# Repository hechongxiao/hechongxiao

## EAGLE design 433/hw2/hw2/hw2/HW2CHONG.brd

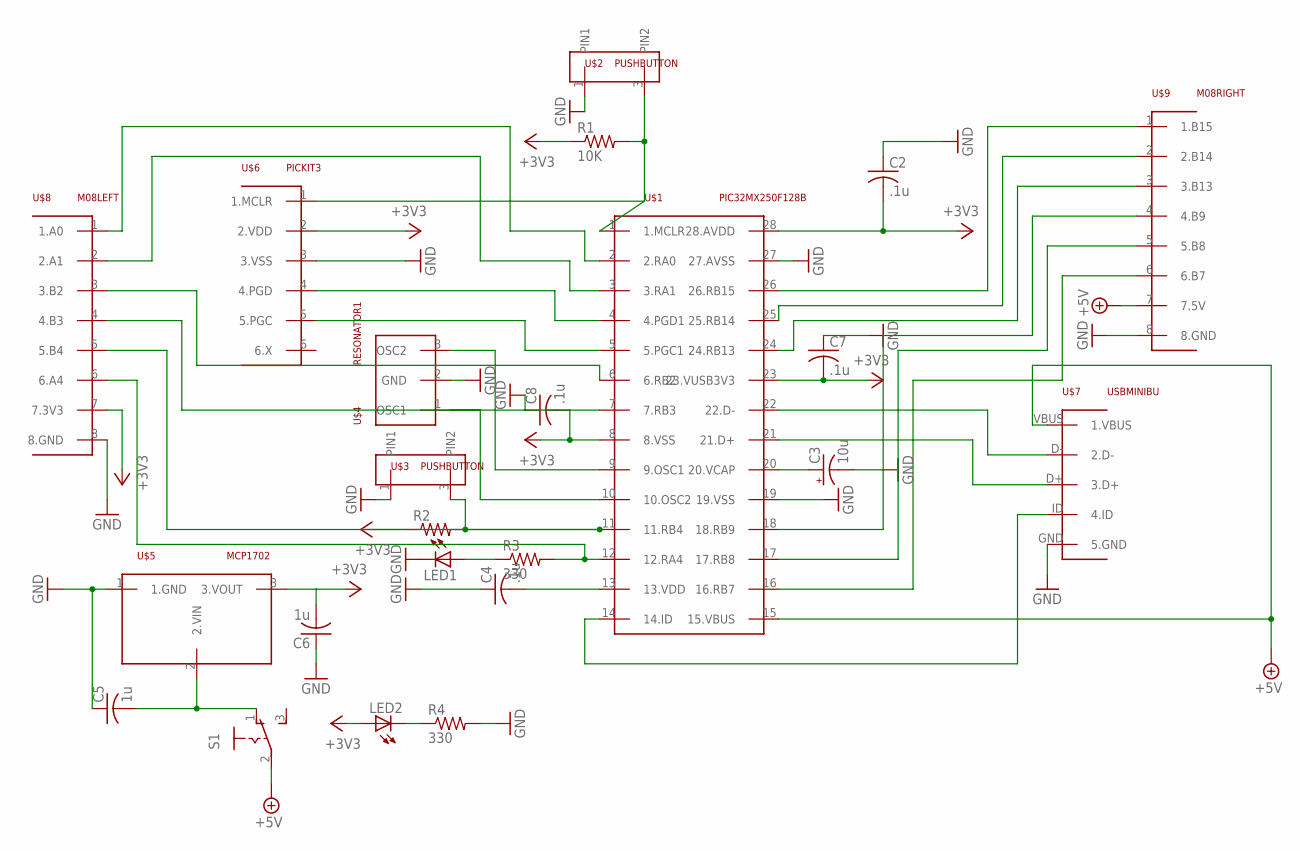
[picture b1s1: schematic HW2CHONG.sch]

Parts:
C2, C4, C7, C8: .1u; C025-025X050
C3: 10u; B45181A
C5, C6: 1u; C025-025X050
LED1, LED2: LED3MM
R1: 10K; 0207/10
R2: R-US_0207/10; 0207/10
R3, R4: 330; 0207/10
S1: 255SB
U$1: PIC32MX250F128B; DIL28-3
U$2, U$3: PUSHBUTTON; 1X03
U$4: RESONATOR1; 1X03
U$5: MCP1702; TO92
U$6: PICKIT3; 1X06
U$7: USBMINIBU; USB-MB-H
U$8: M08LEFT; 1X08
U$9: M08RIGHT; 1X08

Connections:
+3V3: C2.2, C7.2, C8.2, LED2.A, R1.1, R2.1, U$1.8 (8.VSS), U$1.23 (23.VUSB3V3), U$1.28 (28.AVDD), U$6.2 (2.VDD), U$8.7 (7.3V3)
+5V: S1.2, U$1.15 (15.VBUS), U$7.VBUS (1.VBUS), U$9.7 (7.5V)
GND: C2.1, C3.-, C4.1, C5.1, C6.1, C7.1, C8.1, LED1.K (C), R4.2, U$1.19 (19.VSS), U$1.27 (27.AVSS), U$2.1 (PIN1), U$3.1 (PIN1), U$4.2 (GND), U$5.1 (1.GND), U$6.3 (3.VSS), U$7.GND (5.GND), U$8.8 (8.GND), U$9.8 (8.GND)
unnamed: LED1.A, R3.1
unnamed: R3.2, U$1.12 (12.RA4), U$8.6 (6.A4)
unnamed: R1.2, U$1.1 (1.MCLR), U$2.3 (PIN2), U$6.1 (1.MCLR)
unnamed: C3.+, U$1.20 (20.VCAP)
unnamed: R2.2, U$1.11 (11.RB4), U$3.3 (PIN2), U$8.5 (5.B4)
unnamed: C4.2, U$1.13 (13.VDD)
unnamed: C6.2, U$5.3 (3.VOUT)
unnamed: U$1.10 (10.OSC2), U$4.1 (OSC1)
unnamed: U$1.9 (9.OSC1), U$4.3 (OSC2)
unnamed: U$1.4 (4.PGD1), U$6.4 (4.PGD)
unnamed: U$1.5 (5.PGC1), U$6.5 (5.PGC)
unnamed: U$1.22 (22.D-), U$7.D- (2.D-)
unnamed: U$1.21 (21.D+), U$7.D+ (3.D+)
unnamed: U$1.14 (14.ID), U$7.ID (4.ID)
unnamed: U$1.2 (2.RA0), U$8.1 (1.A0)
unnamed: C5.2, S1.1 (O), U$5.2 (2.VIN)
unnamed: LED2.K (C), R4.1
unnamed: U$1.3 (3.RA1), U$8.2 (2.A1)
unnamed: U$1.6 (6.RB2), U$8.3 (3.B2)
unnamed: U$1.7 (7.RB3), U$8.4 (4.B3)
unnamed: U$1.26 (26.RB15), U$9.1 (1.B15)
unnamed: U$1.25 (25.RB14), U$9.2 (2.B14)
unnamed: U$1.24 (24.RB13), U$9.3 (3.B13)
unnamed: U$1.18 (18.RB9), U$9.4 (4.B9)
unnamed: U$1.17 (17.RB8), U$9.5 (5.B8)
unnamed: U$1.16 (16.RB7), U$9.6 (6.B7)

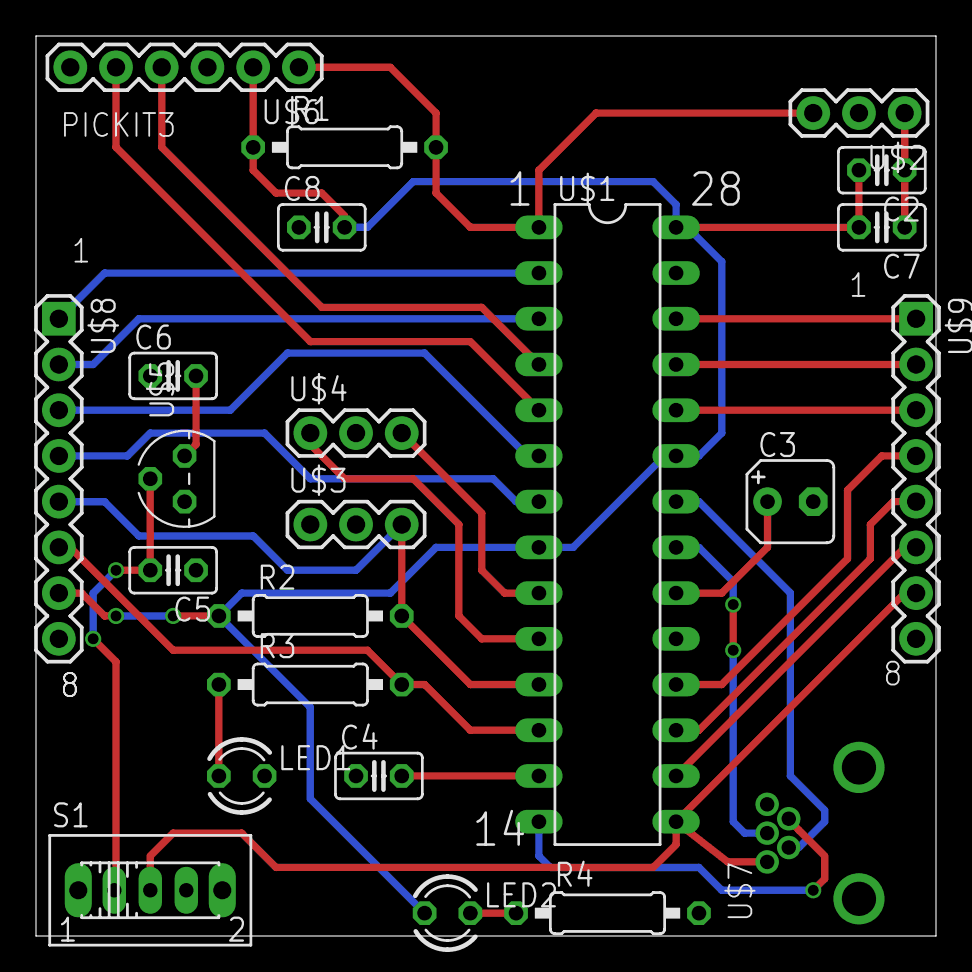
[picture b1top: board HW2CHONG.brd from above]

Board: 2 copper layers, 50.0 x 50.0 mm, 23 parts (0 on the bottom side), 29 nets.

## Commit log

2016-04-14 :neckbeard: Added .gitattributes & .gitignore files
2016-04-26 hw4
    hw3 is actually hw4
2016-06-04 camerea
2016-06-06 hw13
2016-06-10 final projects
